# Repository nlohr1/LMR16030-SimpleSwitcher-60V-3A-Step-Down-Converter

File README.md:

# LMR16030-SimpleSwitcher-60V-3A-Step-Down-Converter

Step-Down-Converter with **real** 3A continuous output current, low heating IC (cooled @ 3A).

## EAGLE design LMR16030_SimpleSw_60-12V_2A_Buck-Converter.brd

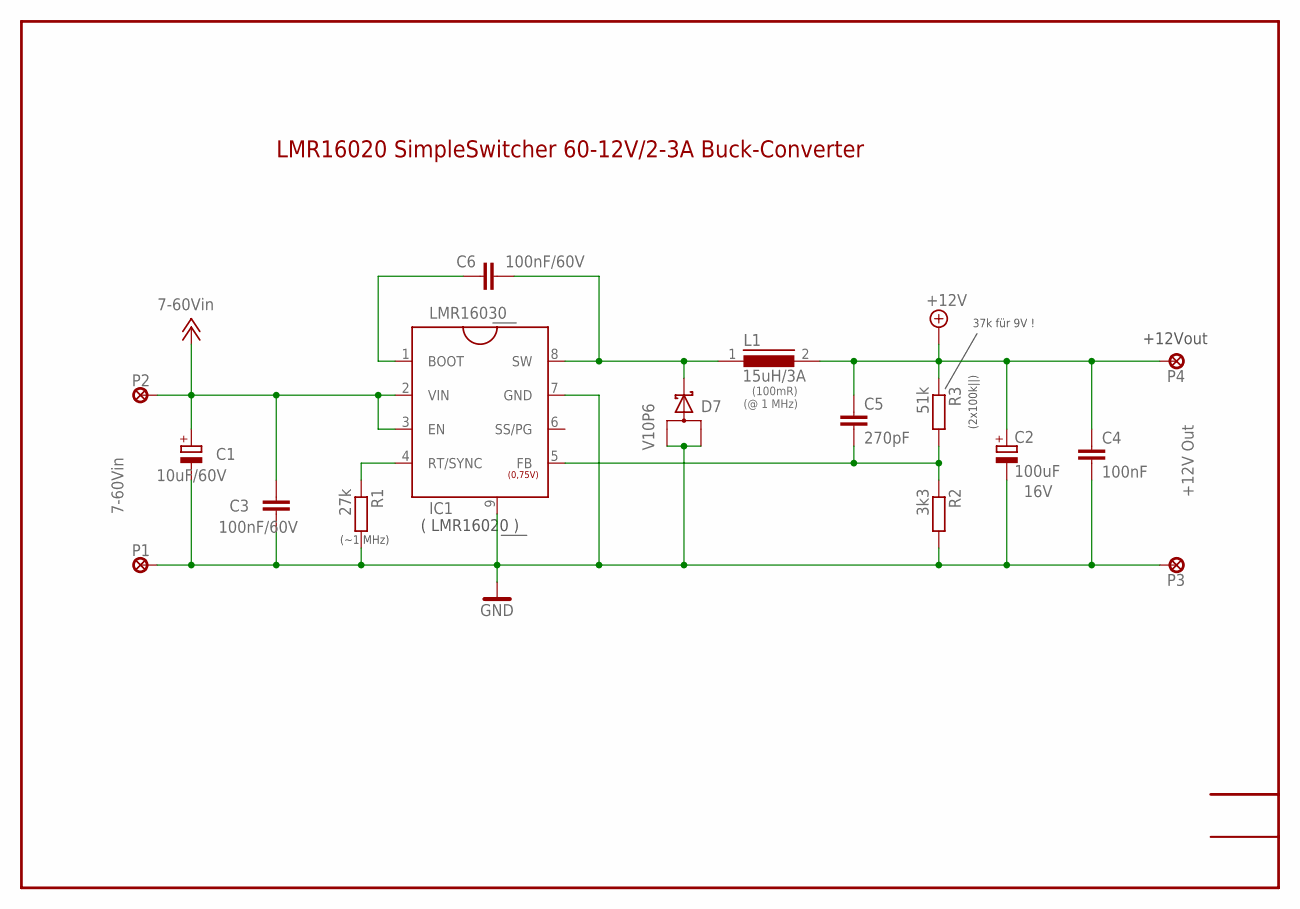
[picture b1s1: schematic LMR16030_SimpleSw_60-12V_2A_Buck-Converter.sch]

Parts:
C1: 10uF/60V; E3,5-8
C2: 100uF; E3,5-8
C3: 100nF/60V; C0805
C4: 100nF; C0805
C5: 270pF; C0603K
C6: 100nF/60V; C0603K
D7: V10P6; TO277A
IC1: LMR16030; SO8-POWERPAD
L1: 15uH/3A; SLF7045
P1, P2, P3, P4: LSP15
R1: 27k; R0805
R2: 3k3; R0805
R3: 51k; R0805

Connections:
+5V: C2.+, C4.1, C5.1, L1.2, P4.P$1, R3.1
+12V: C1.+, C3.1, IC1.2 (VIN), IC1.3 (EN), P2.P$1
GND: C1.-, C2.-, C3.2, C4.2, D7.A@1 (A1), D7.A@2 (A2), IC1.7 (GND), IC1.9, P1.P$1, P3.P$1, R1.2, R2.2
unnamed: IC1.4 (RT/SYNC), R1.1
unnamed: C6.2, D7.K, IC1.8 (SW), L1.1
unnamed: C5.2, IC1.5 (FB), R2.1, R3.2
unnamed: C6.1, IC1.1 (BOOT)

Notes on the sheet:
7-60Vin
(100mR)
(@ 1 MHz)
(~1 MHz)
+12V Out
+12Vout
LMR16020 SimpleSwitcher 60-12V/2-3A Buck-Converter
16V
(0,75V)
( LMR16020 )
(2x100k||)
37k für 9V !

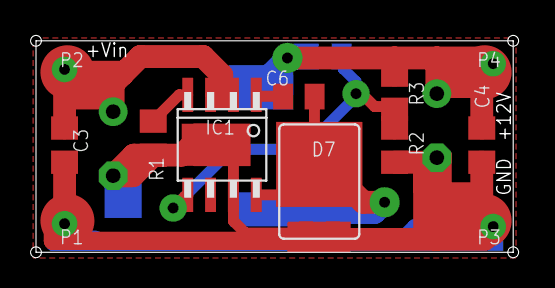
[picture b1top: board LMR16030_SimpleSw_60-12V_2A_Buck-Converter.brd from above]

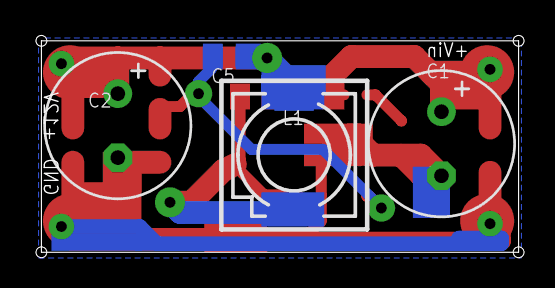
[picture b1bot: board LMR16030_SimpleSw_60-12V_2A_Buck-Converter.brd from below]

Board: 2 copper layers, 26.8 x 12.0 mm, 16 parts (4 on the bottom side), 7 nets.
